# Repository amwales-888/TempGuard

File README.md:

# TempGuard
PID Temperature Controller dsPIC33EV64GM004 Hardware/Firmware 

Initial requirements were to control the temperature of an enclosed system, holding it as close as possible to a set temperature during operation. Venting air out of the enclosure using a FAN would quickly bring the temperature inside the enclosure to match the outside temperature which was unacceptable. Using an MCU we can monitor the temperature and vent air using a fan at a controlled rate. PID algorythms are commonly used in such systems - ['A proportional–integral–derivative controller (PID controller or three-term controller) is a control loop mechanism employing feedback that is widely used in industrial control systems and a variety of other applications requiring continuously modulated control.'](https://en.wikipedia.org/wiki/Proportional%E2%80%93integral%E2%80%93derivative_controller)

[dsPIC33EV64GM004](https://www.microchip.com/en-us/product/dsPIC33EV64GM004) MCU using 20MHz oscllator, configured with 140MHz FOSC ( 70 MIPS ). This device was selected based on pincount, cost and flexibility of its peripherals. It is presented in a surface mount 44pin quad flat pack that is easily hand solderable, along with a respectable 64k of flash and 8k RAM.

- 4 Input Capture devices for interfacing with temp sensors supporting [DHT11](docs/DHT11-Technical-Data-Sheet-Translated-Version-1143054.pdf) and [DHT22](docs/DHT22.pdf) protocols
- 3 2-Channel PWM devices running at 25KHz for controlling [4pin PWN fans](docs/4_Wire_PWM_Spec.pdf). Support for 3pin and 2pin fans using PWM on power pin if required
- 1 UART for communication, loggin with a host, configured at 9600 8N1
- 11 GPIOs connected to [2004 LCD (HD44780)](docs/HD44780.pdf) driven using 8bit Data, RS, RW and Enable, reading busy-flag to ensure maximum output throughput
- 12 GPIOs
  - 2 dedicated to rotary encoder ( GPIO4, GPIO5 )
  - 1 dedicated to a button ( GPIO3 )
  - 3 Inputs used to read TACH from 4PIN and 3PIN fans to calculate RPM 
  - 3 Output to FETs used as low-side switches controlling the FAN 12V power in the case of 3pin and 2pin fans and for power off control of 4pin fans
- 3 spare GPIO0, GPIO1, GPIO2 which can be used for notification of ALARM conditions, ie. FAN not spinning or Sensor not returning data.
- 3 Timers
  - TMR1 used as system timer used to monitor 10ms tick for scheduling
  - TMR3 used by PWM hardware
  - TMR4 used as high frequency timer with 7.3us tick

The system runs with a simple co-operative multitasking round-robin scheduler with a 10ms tick rate and ability to use a second high resultion timer with a 7us period. Tasks can be scheduled with or without a period, added and removed during operation. All tasks are non-blocking.

User interaction is through an LCD display current value from the attached temp sensors and fans. A rotary encoder and button can be used to navigate menus and change settings.

The LCD is updated from an in memory buffer at >120 times a second.

Ouput is also sent via UART over USB for logging purposes.

The firmware was developed usng the Microchip tools, [MPLABX](https://www.microchip.com/en-us/tools-resources/develop/mplab-x-ide) (v6.10) using [XC16](https://www.microchip.com/en-us/tools-resources/develop/mplab-xc-compilers/xc16) (v2.10) compiler and [MCC](https://www.microchip.com/en-us/tools-resources/configure/mplab-code-configurator) (v5) used to generate system, clock and initialisation code for hardware peripherals.

The firmware is written to the MCU in-circuit using a Microchip [Pickit5](https://www.microchip.com/en-us/development-tool/PG164150). Using the Pickit5 it is also possible to do source level debugging of the MCU while in-circuit.

For test and verification the first version of the device was coded on a dsPIC33EV64GM002 28pin DIP version of the device and soldered onto stripboard, the results for a 40minute session were logged, once the enclosure reached the required set temperature their was little to no deviation seen over the 40minutes.

## Hardware/Enclosure

<table>
  <tr>
    <td colspan="2"> </td>
  </tr>
  <tr>
    <td> </td>
    <td> </td>
  </tr>
  <tr>
    <td> </td>
    <td> </td>
  </tr>
  <tr>
    <td> </td>
    <td> </td>
  </tr>
</table>

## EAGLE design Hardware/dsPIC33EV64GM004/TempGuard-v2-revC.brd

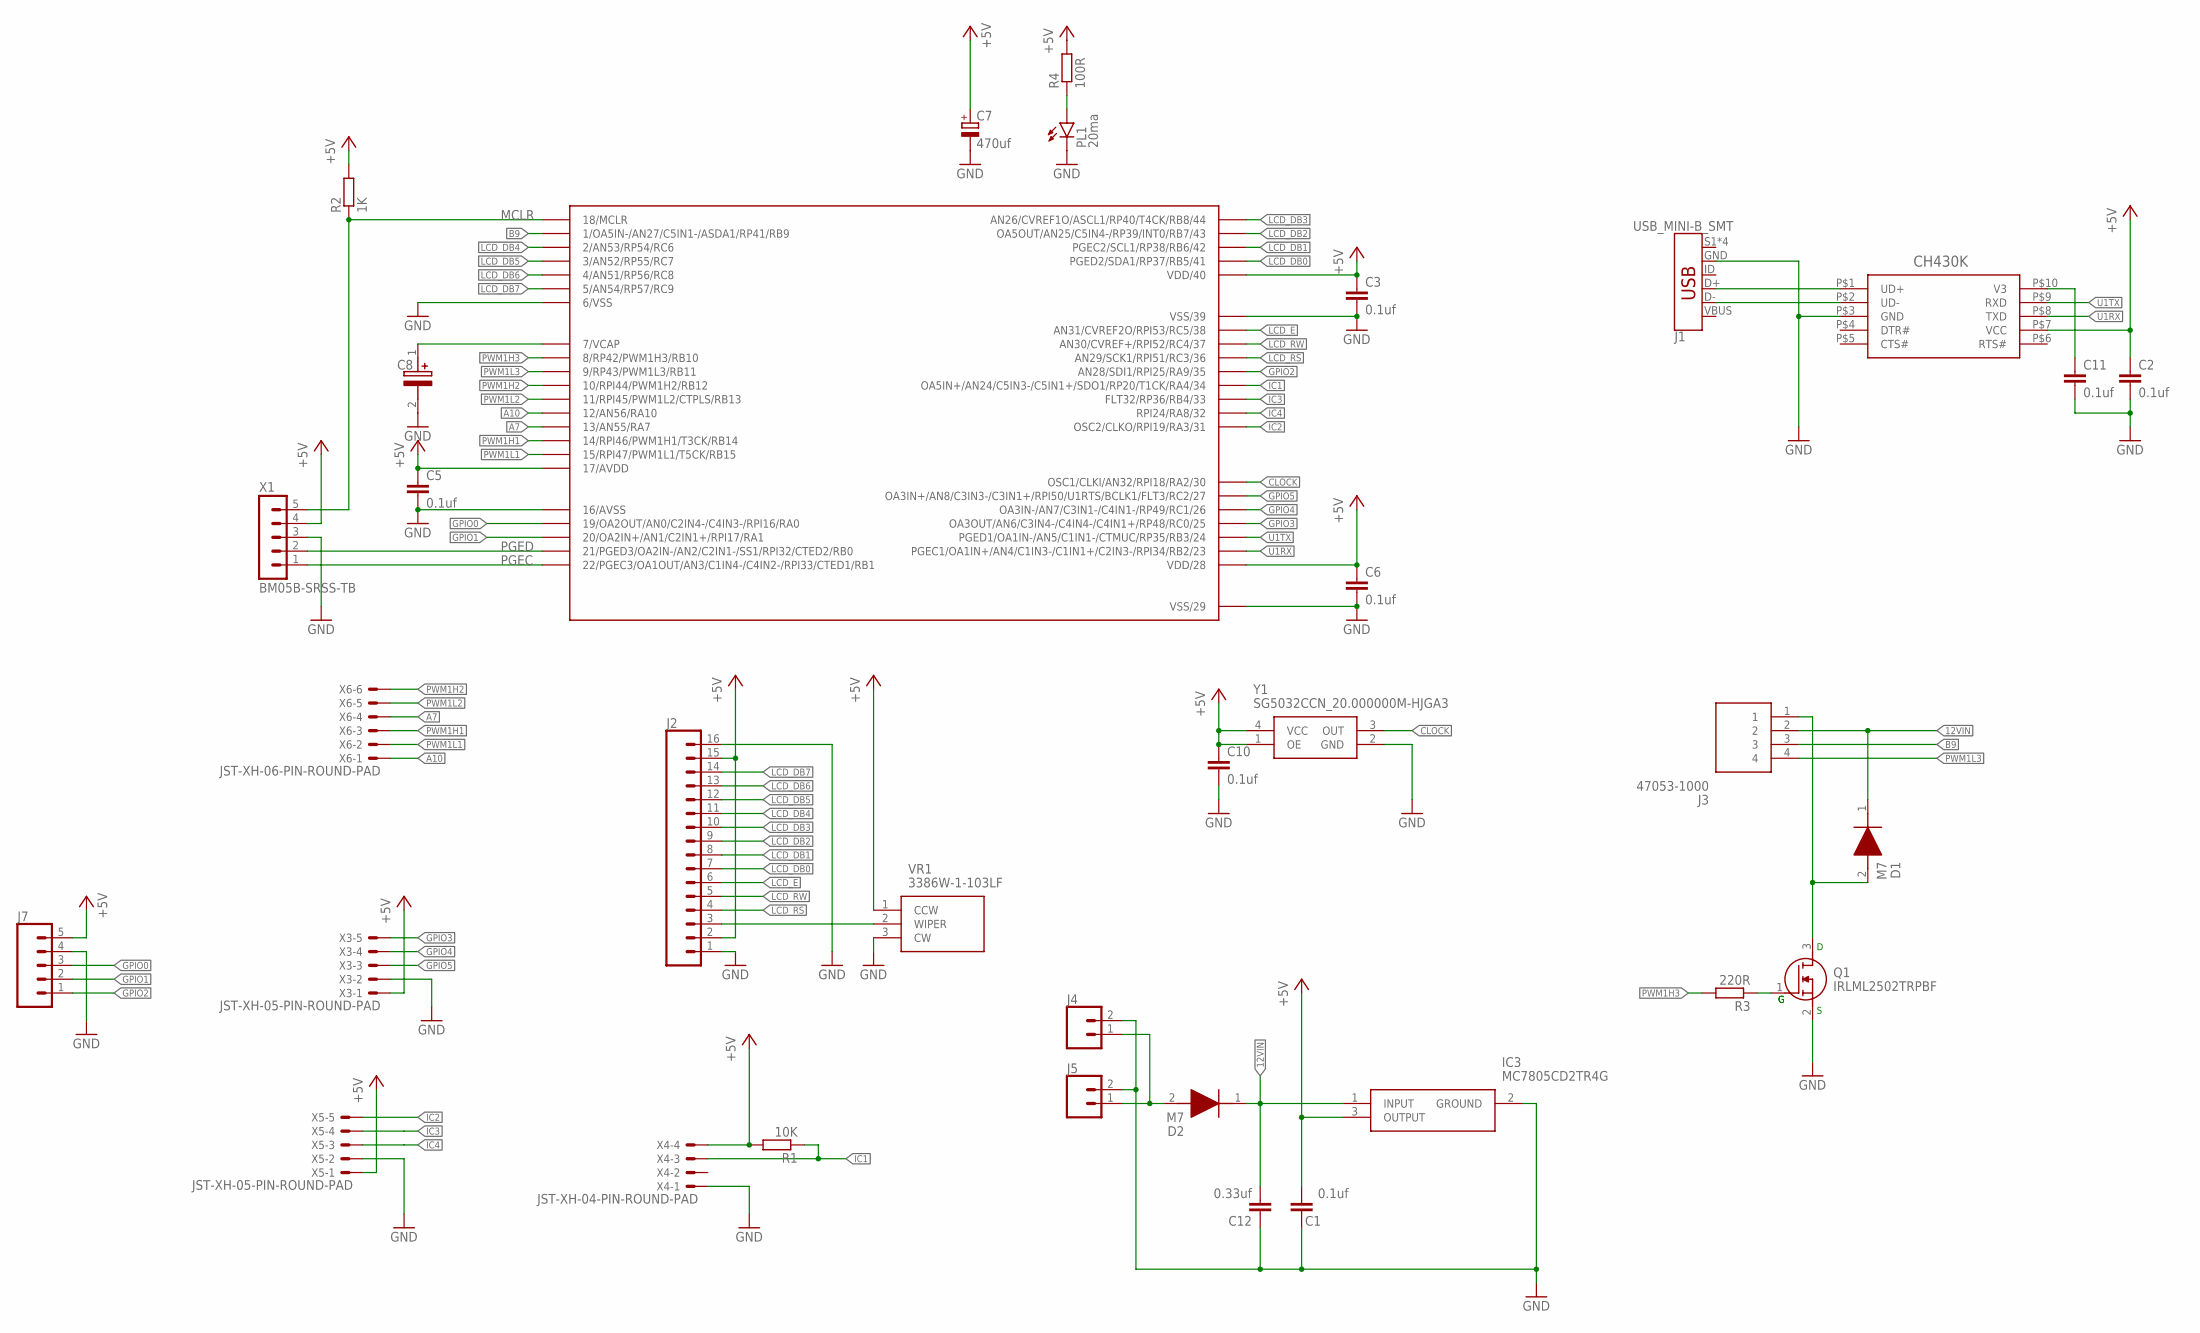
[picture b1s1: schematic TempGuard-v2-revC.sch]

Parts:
C1, C2, C3, C5, C6, C10, C11: 0.1uf; C0805
C7: 470uf; E3,5-8
C8: T491C106K016ATAUTO; T491C
C12: 0.33uf; C1206
D1, D2: M7; DIOM5327X240N
IC3: MC7805CD2TR4G
J1: USB_MINI-B_SMT; USB-MINIB
J2: CONN_16LONGPADS; 1X16_LONGPADS
J3: 47053-1000; 470531000
J4, J5: CONN_025MM; SCREWTERMINAL-5MM-2
J7: CONN_05; 1X05
MCU1: DSPIC33EV64GM004-I/PT; QFP80P1200X1200X120-44
PL1: 20ma; SML0805
Q1: IRLML2502TRPBF; SOT95P237X112-3N
R1: 10K; R0805
R2: 1K; R0805
R3: 220R; R0805
R4: 100R; R0805
U$1: CH430K; ESSOP-10
VR1: 3386W-1-103LF; 3386W
X1: BM05B-SRSS-TB
X3, X5: JST-XH-05-PIN-ROUND-PAD; JST-XH-05-PACKAGE-ROUND-PAD
X4: JST-XH-04-PIN-ROUND-PAD; JST-XH-04-PACKAGE-ROUND-PAD
X6: JST-XH-06-PIN-ROUND-PAD; JST-XH-06-PACKAGE-ROUND-PAD
Y1: SG5032CCN_20.000000M-HJGA3; SG5032CCN20000000MHJGA3

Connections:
12VIN: C12.2, D1.1 (K), D2.1 (K), IC3.1 (INPUT), J3.2
+5V: C1.2, C2.1, C3.1, C5.1, C6.1, C7.+, C10.1, IC3.3 (OUTPUT), J2.2, J2.15, J7.5, MCU1.17 (17/AVDD), MCU1.28 (VDD/28), MCU1.40 (VDD/40), R1.2, R2.2, R4.2, U$1.P$7 (VCC), VR1.1 (CCW), X1.4, X3.1, X4.4, X5.1, Y1.1 (OE), Y1.4 (VCC)
A7: MCU1.13 (13/AN55/RA7), X6.4
A10: MCU1.12 (12/AN56/RA10), X6.1
B9: J3.3, MCU1.1 (1/OA5IN-/AN27/C5IN1-/ASDA1/RP41/RB9)
CLOCK: MCU1.30 (OSC1/CLKI/AN32/RPI18/RA2/30), Y1.3 (OUT)
GND: C1.1, C2.2, C3.2, C5.2, C6.2, C7.-, C8.2 (-), C10.2, C11.2, C12.1, IC3.2 (GROUND), J1.GND, J2.1, J2.16, J4.2, J5.2, J7.4, MCU1.6 (6/VSS), MCU1.16 (16/AVSS), MCU1.29 (VSS/29), MCU1.39 (VSS/39), PL1.C, Q1.2 (S), U$1.P$3 (GND), VR1.3 (CW), X1.3, X3.2, X4.1, X5.2, Y1.2 (GND)
GPIO0: J7.3, MCU1.19 (19/OA2OUT/AN0/C2IN4-/C4IN3-/RPI16/RA0)
GPIO1: J7.2, MCU1.20 (20/OA2IN+/AN1/C2IN1+/RPI17/RA1)
GPIO2: J7.1, MCU1.35 (AN28/SDI1/RPI25/RA9/35)
GPIO3: MCU1.25 (OA3OUT/AN6/C3IN4-/C4IN4-/C4IN1+/RP48/RC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), X3.5
GPIO4: MCU1.26 (OA3IN-/AN7/C3IN1-/C4IN1-/RP49/RC1/26), X3.4
GPIO5: MCU1.27 (OA3IN+/AN8/C3IN3-/C3IN1+/RPI50/U1RTS/BC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), X3.3
IC1: MCU1.34 (OA5IN+/AN24/C5IN3-/C5IN1+/SDO1/RP20/T1C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), R1.1, X4.3
IC2: MCU1.31 (OSC2/CLKO/RPI19/RA3/31), X5.5
IC3: MCU1.33 (FLT32/RP36/RB4/33), X5.4
IC4: MCU1.32 (RPI24/RA8/32), X5.3
LCD_DB0: J2.7, MCU1.41 (PGED2/SDA1/RP37/RB5/41)
LCD_DB1: J2.8, MCU1.42 (PGEC2/SCL1/RP38/RB6/42)
LCD_DB2: J2.9, MCU1.43 (OA5OUT/AN25/C5IN4-/RP39/INT0/RB7/43)
LCD_DB3: J2.10, MCU1.44 (AN26/CVREF1O/ASCL1/RP40/T4CK/RB8/44)
LCD_DB4: J2.11, MCU1.2 (2/AN53/RP54/RC6)
LCD_DB5: J2.12, MCU1.3 (3/AN52/RP55/RC7)
LCD_DB6: J2.13, MCU1.4 (4/AN51/RP56/RC8)
LCD_DB7: J2.14, MCU1.5 (5/AN54/RP57/RC9)
LCD_E: J2.6, MCU1.38 (AN31/CVREF2O/RPI53/RC5/38)
LCD_RS: J2.4, MCU1.36 (AN29/SCK1/RPI51/RC3/36)
LCD_RW: J2.5, MCU1.37 (AN30/CVREF+/RPI52/RC4/37)
MCLR: MCU1.18 (18/MCLR), R2.1, X1.5
unnamed: D1.2 (A), J3.1, Q1.3 (D)
unnamed: J2.3, VR1.2 (WIPER)
unnamed: PL1.A, R4.1
unnamed: Q1.1 (G), R3.1
unnamed: D2.2 (A), J4.1, J5.1
unnamed: C11.1, U$1.P$10 (V3)
PGEC: MCU1.22 (22/PGEC3/OA1OUT/AN3/C1IN4-/C4IN2-/RPI33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), X1.1
PGED: MCU1.21 (21/PGED3/OA2IN-/AN2/C2IN1-/SS1/RPI32/CT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), X1.2
PWM1H1: MCU1.14 (14/RPI46/PWM1H1/T3CK/RB14), X6.3
PWM1H2: MCU1.10 (10/RPI44/PWM1H2/RB12), X6.6
PWM1H3: MCU1.8 (8/RP42/PWM1H3/RB10), R3.2
PWM1L1: MCU1.15 (15/RPI47/PWM1L1/T5CK/RB15), X6.2
PWM1L2: MCU1.11 (11/RPI45/PWM1L2/CTPLS/RB13), X6.5
PWM1L3: J3.4, MCU1.9 (9/RP43/PWM1L3/RB11)
U1RX: MCU1.23 (PGEC1/OA1IN+/AN4/C1IN3-/C1IN1+/C2IN3-/R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), U$1.P$8 (TXD)
U1TX: MCU1.24 (PGED1/OA1IN-/AN5/C1IN1-/CTMUC/RP35/RB3/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), U$1.P$9 (RXD)
USB_N: J1.D-, U$1.P$2 (UD-)
USB_P: J1.D+, U$1.P$1 (UD+)
VBUS: J1.VBUS
VCAP: C8.1 (+), MCU1.7 (7/VCAP)

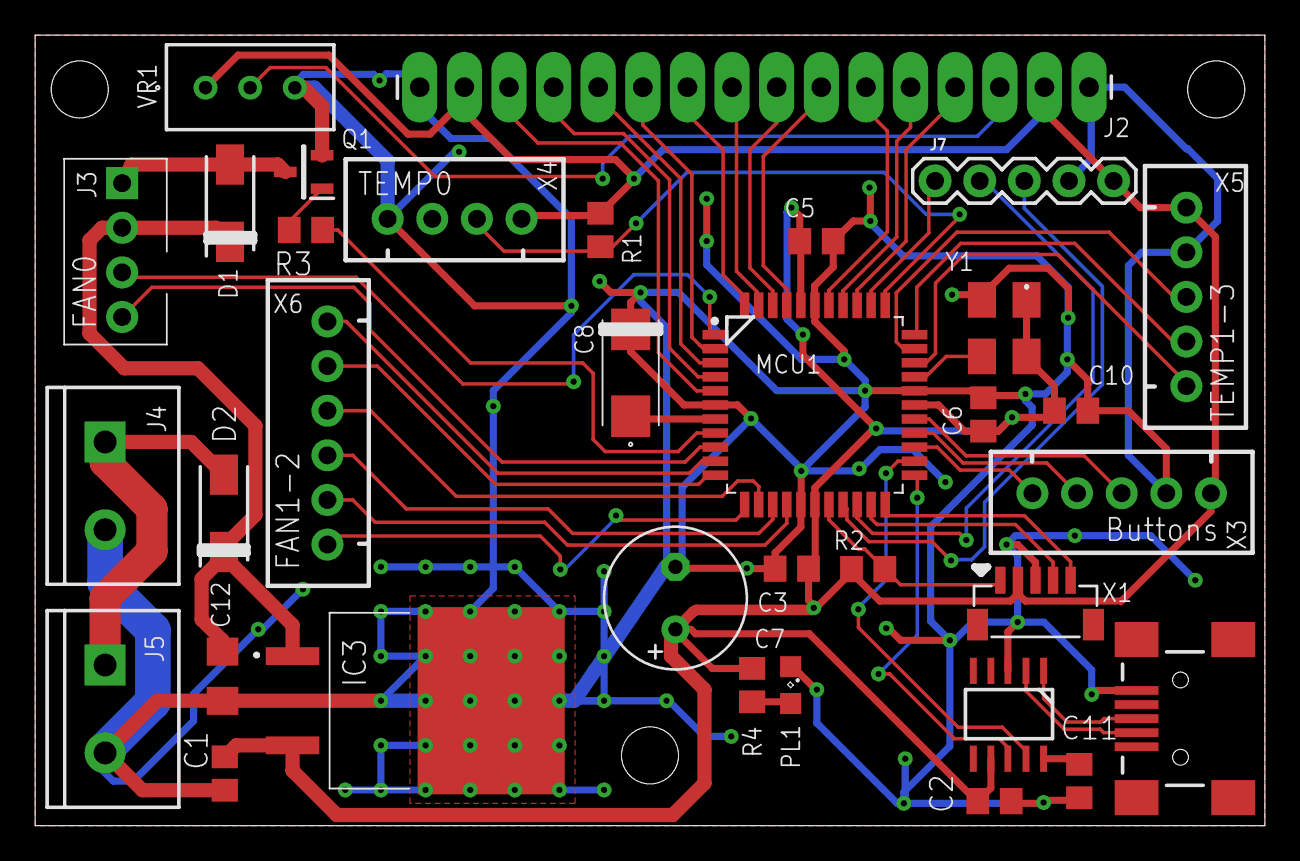
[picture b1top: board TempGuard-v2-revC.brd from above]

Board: 2 copper layers, 70.0 x 45.0 mm, 34 parts (0 on the bottom side), 48 nets.

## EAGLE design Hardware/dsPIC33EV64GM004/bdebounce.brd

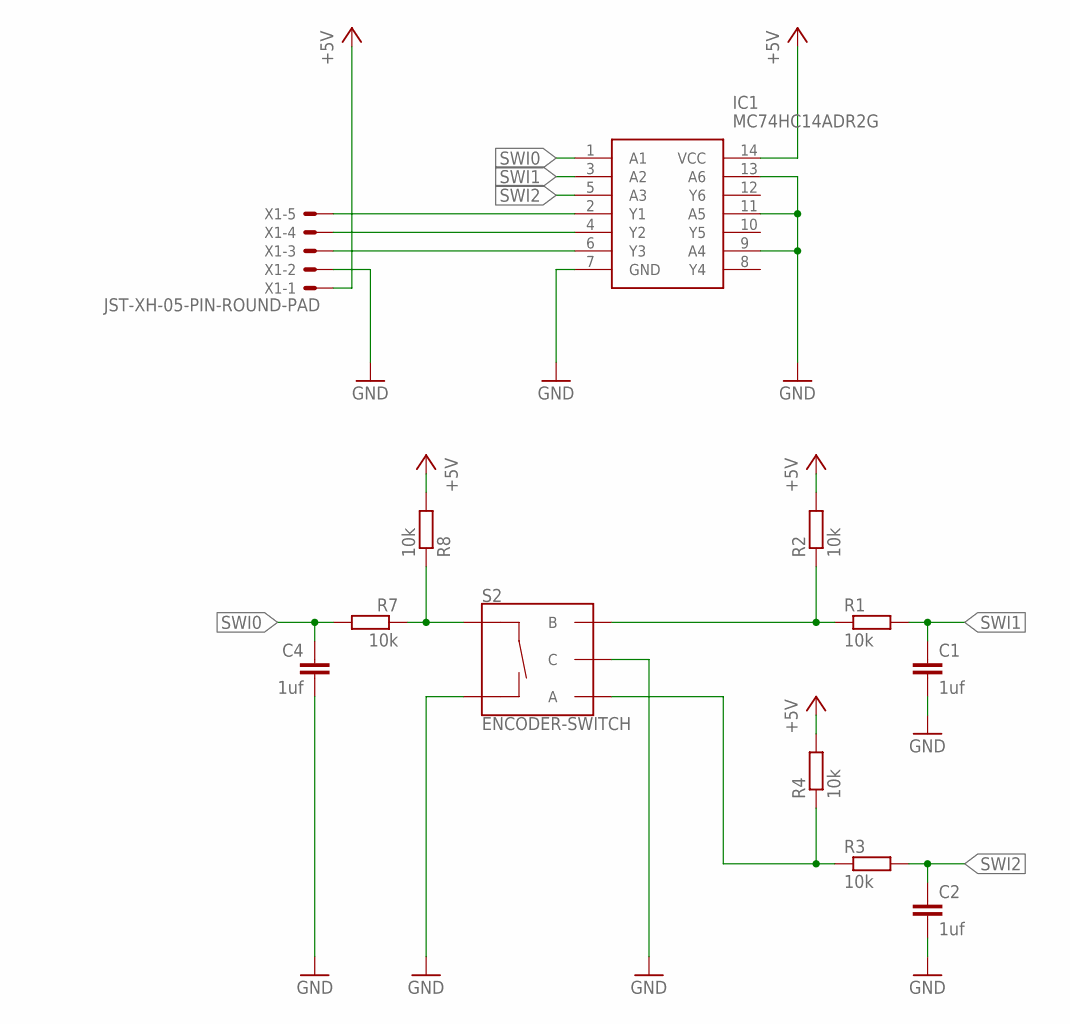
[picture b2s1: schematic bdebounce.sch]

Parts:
C1, C2, C4: 1uf; C0805
IC1: MC74HC14ADR2G; SOIC127P600X175-14N
R1, R2, R3, R4, R7, R8: 10k; R0805
S2: ENCODER-SWITCH; ROTARY_ENC_PLAIN
X1: JST-XH-05-PIN-ROUND-PAD; JST-XH-05-PACKAGE-ROUND-PAD

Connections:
+5V: IC1.14 (VCC), R2.2, R4.2, R8.2, X1.1
GND: C1.2, C2.2, C4.2, IC1.7 (GND), IC1.9 (A4), IC1.11 (A5), IC1.13 (A6), S2.C, S2.SW-, X1.2
unnamed: IC1.6 (Y3), X1.3
SW0: R7.1, R8.1, S2.SW+
SW1: R1.1, R2.1, S2.B
SW2: R3.1, R4.1, S2.A
SWI0: C4.1, IC1.1 (A1), R7.2
SWI1: C1.1, IC1.3 (A2), R1.2
SWI2: C2.1, IC1.5 (A3), R3.2
SWO0: IC1.2 (Y1), X1.5
SWO1: IC1.4 (Y2), X1.4

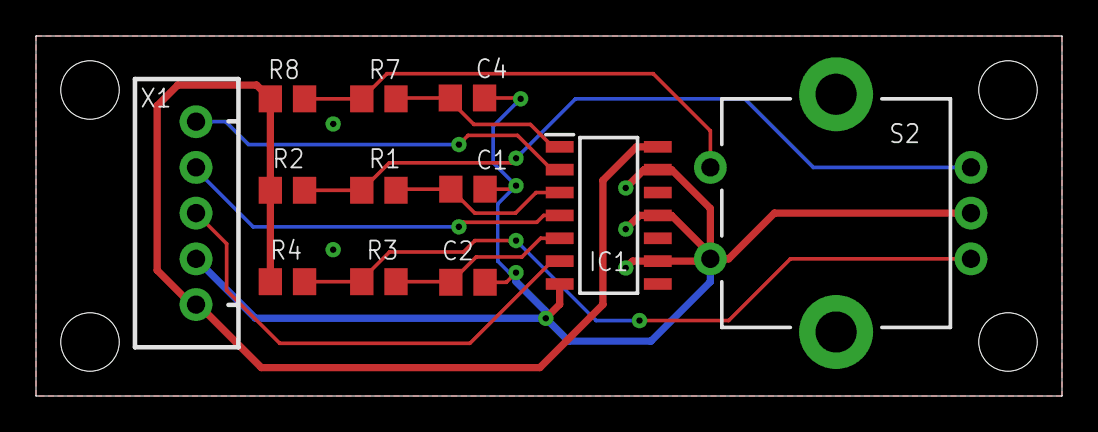
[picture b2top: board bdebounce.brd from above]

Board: 2 copper layers, 57.0 x 20.0 mm, 12 parts (0 on the bottom side), 11 nets.

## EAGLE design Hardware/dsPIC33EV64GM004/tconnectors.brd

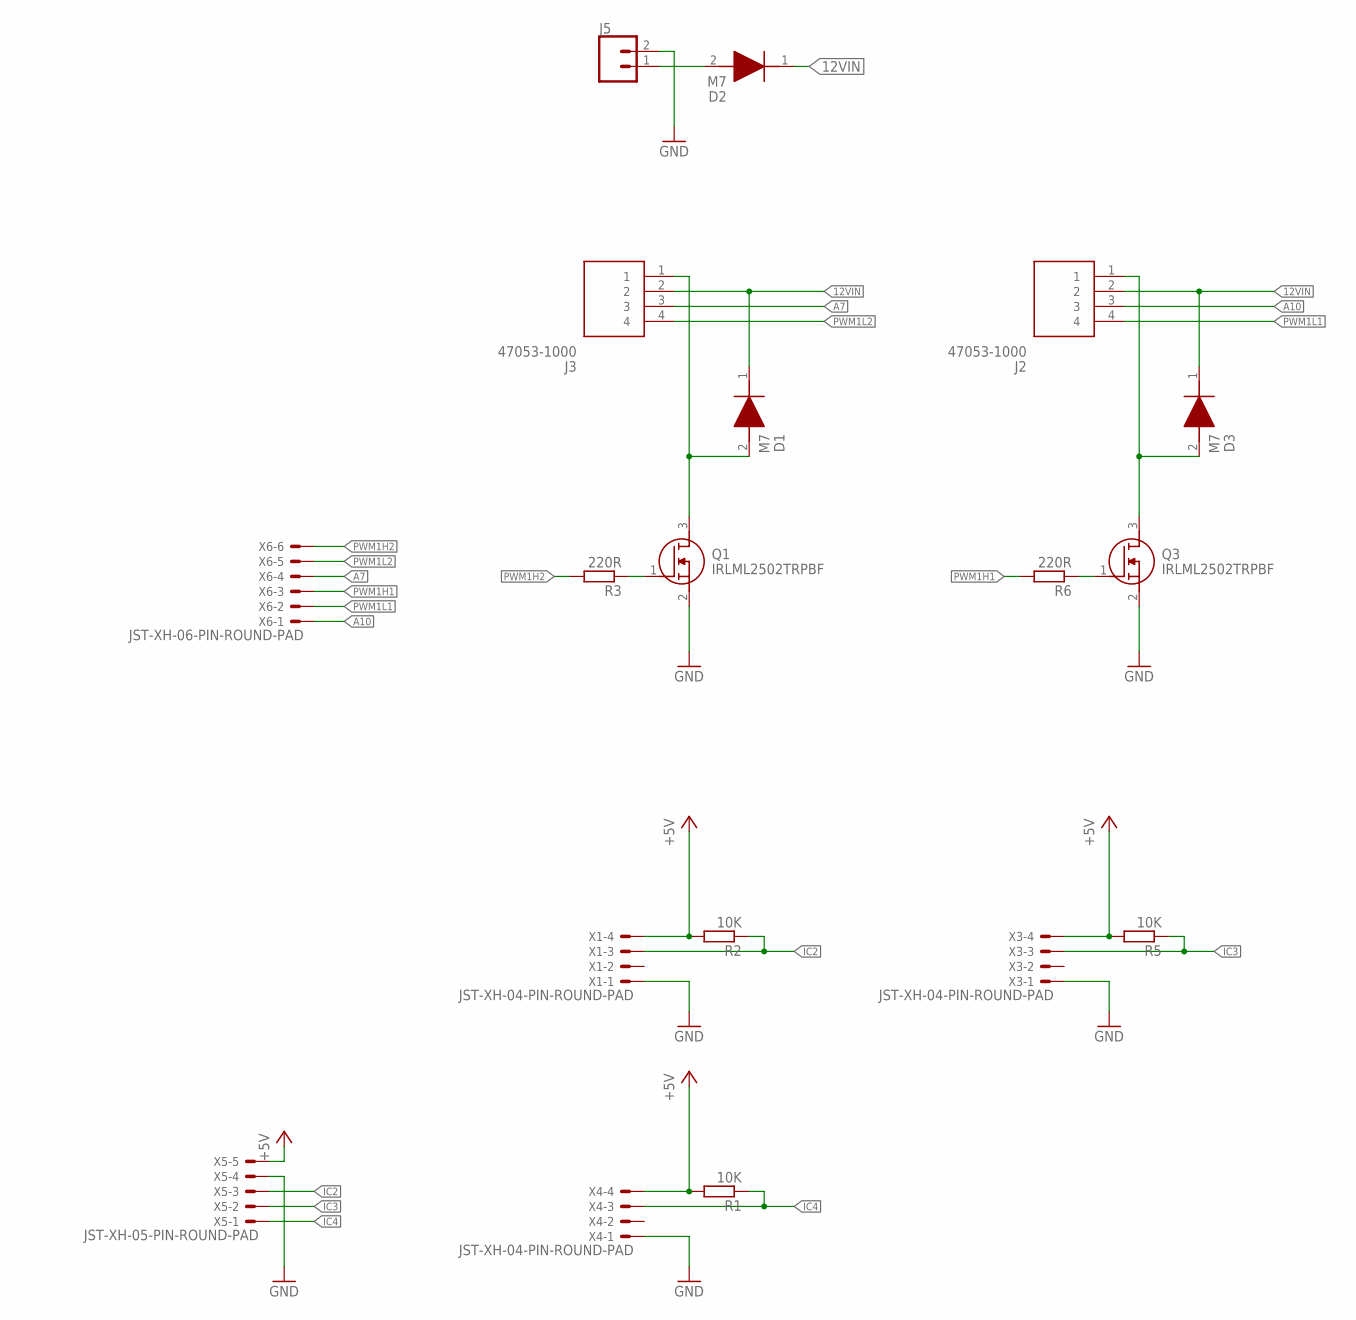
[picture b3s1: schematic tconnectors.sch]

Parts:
D1, D2, D3: M7; DIOM5327X240N
J2, J3: 47053-1000; 470531000
J5: CONN_025MM; SCREWTERMINAL-5MM-2
Q1, Q3: IRLML2502TRPBF; SOT95P237X112-3N
R1, R2, R5: 10K; R0805
R3, R6: 220R; R0805
X1, X3, X4: JST-XH-04-PIN-ROUND-PAD; JST-XH-04-PACKAGE-ROUND-PAD
X5: JST-XH-05-PIN-ROUND-PAD; JST-XH-05-PACKAGE-ROUND-PAD
X6: JST-XH-06-PIN-ROUND-PAD; JST-XH-06-PACKAGE-ROUND-PAD

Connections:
12VIN: D1.1 (K), D2.1 (K), D3.1 (K), J2.2, J3.2
+5V: R1.2, R2.2, R5.2, X1.4, X3.4, X4.4, X5.5
A7: J3.3, X6.4
A10: J2.3, X6.1
GND: J5.2, Q1.2 (S), Q3.2 (S), X1.1, X3.1, X4.1, X5.4
IC2: R2.1, X1.3, X5.3
IC3: R5.1, X3.3, X5.2
IC4: R1.1, X4.3, X5.1
unnamed: D1.2 (A), J3.1, Q1.3 (D)
unnamed: D3.2 (A), J2.1, Q3.3 (D)
unnamed: Q3.1 (G), R6.1
unnamed: Q1.1 (G), R3.1
unnamed: D2.2 (A), J5.1
PWM1H1: R6.2, X6.3
PWM1H2: R3.2, X6.6
PWM1L1: J2.4, X6.2
PWM1L2: J3.4, X6.5

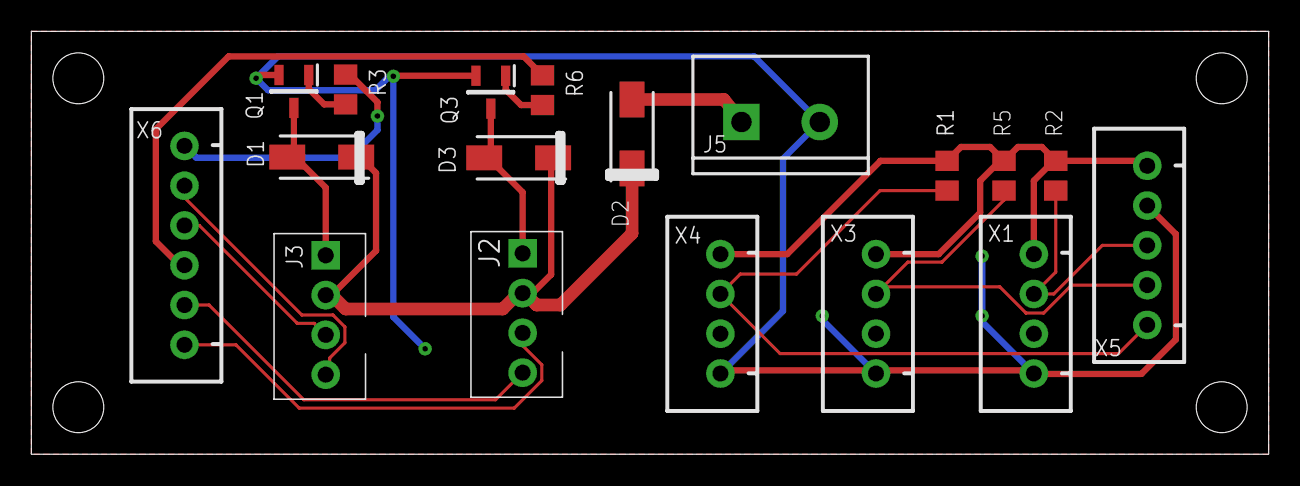
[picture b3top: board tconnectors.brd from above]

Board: 2 copper layers, 79.0 x 27.0 mm, 18 parts (0 on the bottom side), 17 nets.

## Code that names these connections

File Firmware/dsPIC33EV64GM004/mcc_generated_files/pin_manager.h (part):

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*/
/**
  @Summary
    Sets the GPIO pin, RA0, high using LATA0.

  @Description
    Sets the GPIO pin, RA0, high using LATA0.

  @Preconditions
    The RA0 must be set to an output.
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#define GPIO0_SetHigh()          (_LATA0 = 1)
/**
  @Summary
    Sets the GPIO pin, RA0, low using LATA0.

  @Description
    Sets the GPIO pin, RA0, low using LATA0.

  @Preconditions
    The RA0 must be set to an output.
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#define GPIO0_SetLow()           (_LATA0 = 0)
/**
  @Summary
    Toggles the GPIO pin, RA0, using LATA0.

  @Description
    Toggles the GPIO pin, RA0, using LATA0.

  @Preconditions
    The RA0 must be set to an output.
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#define GPIO0_Toggle()           (_LATA0 ^= 1)
/**
  @Summary
    Reads the value of the GPIO pin, RA0.

  @Description
    Reads the value of the GPIO pin, RA0.

  @Preconditions
    None.
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    </code>

*/
#define GPIO0_GetValue()         _RA0
/**
  @Summary
    Configures the GPIO pin, RA0, as an input.

  @Description
    Configures the GPIO pin, RA0, as an input.

  @Preconditions
    None.
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#define GPIO0_SetDigitalInput()  (_TRISA0 = 1)
/**
  @Summary
    Configures the GPIO pin, RA0, as an output.

  @Description
    Configures the GPIO pin, RA0, as an output.

  @Preconditions
    None.
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#define GPIO0_SetDigitalOutput() (_TRISA0 = 0)
/**
  @Summary
    Sets the GPIO pin, RA1, high using LATA1.

  @Description
    Sets the GPIO pin, RA1, high using LATA1.

  @Preconditions
    The RA1 must be set to an output.
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#define GPIO1_SetHigh()          (_LATA1 = 1)
/**
  @Summary
    Sets the GPIO pin, RA1, low using LATA1.

  @Description
    Sets the GPIO pin, RA1, low using LATA1.

  @Preconditions
    The RA1 must be set to an output.
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#define GPIO1_SetLow()           (_LATA1 = 0)
/**
  @Summary
    Toggles the GPIO pin, RA1, using LATA1.

  @Description
    Toggles the GPIO pin, RA1, using LATA1.

  @Preconditions
    The RA1 must be set to an output.
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#define GPIO1_Toggle()           (_LATA1 ^= 1)
/**
  @Summary
    Reads the value of the GPIO pin, RA1.

  @Description
    Reads the value of the GPIO pin, RA1.

  @Preconditions
    None.
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    </code>

*/
#define GPIO1_GetValue()         _RA1
/**
  @Summary
    Configures the GPIO pin, RA1, as an input.

  @Description
    Configures the GPIO pin, RA1, as an input.

  @Preconditions
    None.
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#define GPIO1_SetDigitalInput()  (_TRISA1 = 1)
/**
  @Summary
    Configures the GPIO pin, RA1, as an output.

  @Description
    Configures the GPIO pin, RA1, as an output.

  @Preconditions
    None.
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#define GPIO1_SetDigitalOutput() (_TRISA1 = 0)
/**
  @Summary
    Sets the GPIO pin, RA10, high using LATA10.

  @Description
    Sets the GPIO pin, RA10, high using LATA10.

  @Preconditions
    The RA10 must be set to an output.
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#define TACH2_SetHigh()          (_LATA10 = 1)
/**
  @Summary
    Sets the GPIO pin, RA10, low using LATA10.

  @Description
    Sets the GPIO pin, RA10, low using LATA10.

  @Preconditions
    The RA10 must be set to an output.
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#define TACH2_SetLow()           (_LATA10 = 0)
/**
  @Summary
    Toggles the GPIO pin, RA10, using LATA10.

  @Description
    Toggles the GPIO pin, RA10, using LATA10.

  @Preconditions
    The RA10 must be set to an output.
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#define TACH2_Toggle()           (_LATA10 ^= 1)
/**
  @Summary
    Reads the value of the GPIO pin, RA10.

  @Description
    Reads the value of the GPIO pin, RA10.

  @Preconditions
    None.
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    </code>

*/
#define TACH2_GetValue()         _RA10
/**
  @Summary
    Configures the GPIO pin, RA10, as an input.

  @Description
    Configures the GPIO pin, RA10, as an input.

  @Preconditions
    None.
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#define TACH2_SetDigitalInput()  (_TRISA10 = 1)
/**
  @Summary
    Configures the GPIO pin, RA10, as an output.

  @Description
    Configures the GPIO pin, RA10, as an output.

  @Preconditions
    None.
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#define TACH2_SetDigitalOutput() (_TRISA10 = 0)
/**
  @Summary
    Sets the GPIO pin, RA7, high using LATA7.

  @Description
    Sets the GPIO pin, RA7, high using LATA7.

  @Preconditions
    The RA7 must be set to an output.
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#define TACH1_SetHigh()          (_LATA7 = 1)
/**
  @Summary
    Sets the GPIO pin, RA7, low using LATA7.

  @Description
    Sets the GPIO pin, RA7, low using LATA7.

  @Preconditions
    The RA7 must be set to an output.
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#define TACH1_SetLow()           (_LATA7 = 0)
/**
  @Summary
    Toggles the GPIO pin, RA7, using LATA7.

  @Description
    Toggles the GPIO pin, RA7, using LATA7.

  @Preconditions
    The RA7 must be set to an output.
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#define TACH1_Toggle()           (_LATA7 ^= 1)
/**
  @Summary
    Reads the value of the GPIO pin, RA7.

  @Description
    Reads the value of the GPIO pin, RA7.

  @Preconditions
    None.
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    </code>

*/
#define TACH1_GetValue()         _RA7
/**
  @Summary
    Configures the GPIO pin, RA7, as an input.

  @Description
    Configures the GPIO pin, RA7, as an input.

  @Preconditions
    None.
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#define TACH1_SetDigitalInput()  (_TRISA7 = 1)
/**
  @Summary
    Configures the GPIO pin, RA7, as an output.

  @Description
    Configures the GPIO pin, RA7, as an output.

  @Preconditions
    None.
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#define TACH1_SetDigitalOutput() (_TRISA7 = 0)
/**
  @Summary
    Sets the GPIO pin, RA9, high using LATA9.

  @Description
    Sets the GPIO pin, RA9, high using LATA9.

  @Preconditions
    The RA9 must be set to an output.
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#define GPIO2_SetHigh()          (_LATA9 = 1)
/**
  @Summary
    Sets the GPIO pin, RA9, low using LATA9.

  @Description
    Sets the GPIO pin, RA9, low using LATA9.

  @Preconditions
    The RA9 must be set to an output.
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#define GPIO2_SetLow()           (_LATA9 = 0)
/**
  @Summary
    Toggles the GPIO pin, RA9, using LATA9.

  @Description
    Toggles the GPIO pin, RA9, using LATA9.

  @Preconditions
    The RA9 must be set to an output.
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#define GPIO2_Toggle()           (_LATA9 ^= 1)
/**
  @Summary
    Reads the value of the GPIO pin, RA9.

  @Description
    Reads the value of the GPIO pin, RA9.

  @Preconditions
    None.
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    </code>

*/
#define GPIO2_GetValue()         _RA9
/**
  @Summary
    Configures the GPIO pin, RA9, as an input.

  @Description
    Configures the GPIO pin, RA9, as an input.

  @Preconditions
    None.
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#define GPIO2_SetDigitalInput()  (_TRISA9 = 1)
/**
  @Summary
    Configures the GPIO pin, RA9, as an output.

  @Description
    Configures the GPIO pin, RA9, as an output.

  @Preconditions
    None.
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#define GPIO2_SetDigitalOutput() (_TRISA9 = 0)
/**
  @Summary
    Sets the GPIO pin, RB5, high using LATB5.

  @Description
    Sets the GPIO pin, RB5, high using LATB5.

  @Preconditions
    The RB5 must be set to an output.
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#define LCD_DB0_SetHigh()          (_LATB5 = 1)
/**
  @Summary
    Sets the GPIO pin, RB5, low using LATB5.

  @Description
    Sets the GPIO pin, RB5, low using LATB5.

  @Preconditions
    The RB5 must be set to an output.
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#define LCD_DB0_SetLow()           (_LATB5 = 0)
/**
  @Summary
    Toggles the GPIO pin, RB5, using LATB5.

  @Description
    Toggles the GPIO pin, RB5, using LATB5.

  @Preconditions
    The RB5 must be set to an output.
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#define LCD_DB0_Toggle()           (_LATB5 ^= 1)
/**
  @Summary
    Reads the value of the GPIO pin, RB5.

  @Description
    Reads the value of the GPIO pin, RB5.

  @Preconditions
    None.
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    </code>

*/
#define LCD_DB0_GetValue()         _RB5
/**
  @Summary
    Configures the GPIO pin, RB5, as an input.

  @Description
    Configures the GPIO pin, RB5, as an input.

  @Preconditions
    None.
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#define LCD_DB0_SetDigitalInput()  (_TRISB5 = 1)
/**
  @Summary
    Configures the GPIO pin, RB5, as an output.

  @Description
    Configures the GPIO pin, RB5, as an output.

  @Preconditions
    None.
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#define LCD_DB0_SetDigitalOutput() (_TRISB5 = 0)
/**
  @Summary
    Sets the GPIO pin, RB6, high using LATB6.

  @Description
    Sets the GPIO pin, RB6, high using LATB6.

  @Preconditions
    The RB6 must be set to an output.
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#define LCD_DB1_SetHigh()          (_LATB6 = 1)
/**
  @Summary
    Sets the GPIO pin, RB6, low using LATB6.

  @Description
    Sets the GPIO pin, RB6, low using LATB6.

  @Preconditions
    The RB6 must be set to an output.
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#define LCD_DB1_SetLow()           (_LATB6 = 0)
/**
  @Summary
    Toggles the GPIO pin, RB6, using LATB6.

  @Description
    Toggles the GPIO pin, RB6, using LATB6.

  @Preconditions
    The RB6 must be set to an output.
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#define LCD_DB1_Toggle()           (_LATB6 ^= 1)
/**
  @Summary
    Reads the value of the GPIO pin, RB6.

  @Description
    Reads the value of the GPIO pin, RB6.

  @Preconditions
    None.
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    </code>

*/
#define LCD_DB1_GetValue()         _RB6
/**
  @Summary
    Configures the GPIO pin, RB6, as an input.

  @Description
    Configures the GPIO pin, RB6, as an input.

  @Preconditions
    None.
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#define LCD_DB1_SetDigitalInput()  (_TRISB6 = 1)
/**
  @Summary
    Configures the GPIO pin, RB6, as an output.

  @Description
    Configures the GPIO pin, RB6, as an output.

  @Preconditions
    None.
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#define LCD_DB1_SetDigitalOutput() (_TRISB6 = 0)
/**
  @Summary
    Sets the GPIO pin, RB7, high using LATB7.

  @Description
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
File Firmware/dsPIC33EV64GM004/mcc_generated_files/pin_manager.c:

/**
  PIN MANAGER Generated Driver File

  @Company:
    Microchip Technology Inc.

  @File Name:
    pin_manager.c

  @Summary:
    This is the generated manager file for the PIC24 / dsPIC33 / PIC32MM MCUs device.  This manager
    configures the pins direction, initial state, analog setting.
    The peripheral pin select, PPS, configuration is also handled by this manager.

  @Description:
    This source file provides implementations for PIN MANAGER.
    Generation Information :
        Product Revision  :  PIC24 / dsPIC33 / PIC32MM MCUs - 1.171.4
        Device            :  dsPIC33EV64GM004
    The generated drivers are tested against the following:
        Compiler          :  XC16 v2.10
        MPLAB 	          :  MPLAB X v6.05
*/

/*
    (c) 2020 Microchip Technology Inc. and its subsidiaries. You may use this
    software and any derivatives exclusively with Microchip products.

    THIS SOFTWARE IS SUPPLIED BY MICROCHIP "AS IS". NO WARRANTIES, WHETHER
    EXPRESS, IMPLIED OR STATUTORY, APPLY TO THIS SOFTWARE, INCLUDING ANY IMPLIED
    WARRANTIES OF NON-INFRINGEMENT, MERCHANTABILITY, AND FITNESS FOR A
    PARTICULAR PURPOSE, OR ITS INTERACTION WITH MICROCHIP PRODUCTS, COMBINATION
    WITH ANY OTHER PRODUCTS, OR USE IN ANY APPLICATION.

    IN NO EVENT WILL MICROCHIP BE LIABLE FOR ANY INDIRECT, SPECIAL, PUNITIVE,
    INCIDENTAL OR CONSEQUENTIAL LOSS, DAMAGE, COST OR EXPENSE OF ANY KIND
    WHATSOEVER RELATED TO THE SOFTWARE, HOWEVER CAUSED, EVEN IF MICROCHIP HAS
    BEEN ADVISED OF THE POSSIBILITY OR THE DAMAGES ARE FORESEEABLE. TO THE
    FULLEST EXTENT ALLOWED BY LAW, MICROCHIP'S TOTAL LIABILITY ON ALL CLAIMS IN
    ANY WAY RELATED TO THIS SOFTWARE WILL NOT EXCEED THE AMOUNT OF FEES, IF ANY,
    THAT YOU HAVE PAID DIRECTLY TO MICROCHIP FOR THIS SOFTWARE.

    MICROCHIP PROVIDES THIS SOFTWARE CONDITIONALLY UPON YOUR ACCEPTANCE OF THESE
    TERMS.
*/


/**
    Section: Includes
*/

#include <xc.h>
#include <stdio.h>
#include "pin_manager.h"

/**
 Section: File specific functions
*/
void (*CN_InterruptHandler)(void) = NULL;

/**
 Section: Driver Interface Function Definitions
*/
void PIN_MANAGER_Initialize (void)
{
    /****************************************************************************
     * Setting the Output Latch SFR(s)
     ***************************************************************************/
    LATA = 0x0000;
    LATB = 0x0008;
    LATC = 0x0000;

    /****************************************************************************
     * Setting the GPIO Direction SFR(s)
     ***************************************************************************/
    TRISA = 0x059C;
    TRISB = 0x0217;
    TRISC = 0x0007;

    /****************************************************************************
     * Setting the Weak Pull Up and Weak Pull Down SFR(s)
     ***************************************************************************/
    CNPDA = 0x0000;
    CNPDB = 0x0000;
    CNPDC = 0x0000;
    CNPUA = 0x0480;
    CNPUB = 0x0200;
    CNPUC = 0x0000;

    /****************************************************************************
     * Setting the Open Drain SFR(s)
     ***************************************************************************/
    ODCA = 0x0000;
    ODCB = 0x0000;
    ODCC = 0x0000;

    /****************************************************************************
     * Setting the Analog/Digital Configuration SFR(s)
     ***************************************************************************/
    ANSELA = 0x0000;
    ANSELB = 0x0000;
    ANSELC = 0x0000;
    
    /****************************************************************************
     * Set the PPS
     ***************************************************************************/
    __builtin_write_OSCCONL(OSCCON & 0xbf); // unlock PPS

    RPINR7bits.IC1R = 0x0014;    //RA4->IC1:IC1
    RPINR8bits.IC4R = 0x0018;    //RA8->IC4:IC4
    RPOR0bits.RP35R = 0x0001;    //RB3->UART1:U1TX
    RPINR8bits.IC3R = 0x0024;    //RB4->IC3:IC3
    RPINR7bits.IC2R = 0x0013;    //RA3->IC2:IC2
    RPINR18bits.U1RXR = 0x0022;    //RB2->UART1:U1RX

    __builtin_write_OSCCONL(OSCCON | 0x40); // lock PPS
    
    /****************************************************************************
     * Interrupt On Change: any
     ***************************************************************************/
    CNENAbits.CNIEA10 = 1;    //Pin : RA10
    CNENAbits.CNIEA7 = 1;    //Pin : RA7
    CNENBbits.CNIEB9 = 1;    //Pin : RB9
    
    /* Initialize IOC Interrupt Handler*/
    CN_SetInterruptHandler(&CN_CallBack);
    
    /****************************************************************************
     * Interrupt On Change: Interrupt Enable
     ***************************************************************************/
    IFS1bits.CNIF = 0; //Clear CNI interrupt flag
    IEC1bits.CNIE = 1; //Enable CNI interrupt
}

void __attribute__ ((weak)) CN_CallBack(void)
{

}

void CN_SetInterruptHandler(void (* InterruptHandler)(void))
{ 
    IEC1bits.CNIE = 0; //Disable CNI interrupt
    CN_InterruptHandler = InterruptHandler; 
    IEC1bits.CNIE = 1; //Enable CNI interrupt
}

void CN_SetIOCInterruptHandler(void *handler)
{ 
    CN_SetInterruptHandler(handler);
}

/* Interrupt service routine for the CNI interrupt. */
void __attribute__ (( interrupt, no_auto_psv )) _CNInterrupt ( void )
{
    if(IFS1bits.CNIF == 1)
    {
        if(CN_InterruptHandler) 
        { 
            CN_InterruptHandler(); 
        }
        
        // Clear the flag
        IFS1bits.CNIF = 0;
    }
}

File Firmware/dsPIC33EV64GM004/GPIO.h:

/* 
 *  Copyright (c) 2023 Angelo Masci
 * 
 * Permission is hereby granted, free of charge, to any person obtaining a copy
 * of this software and associated documentation files (the "Software"), to deal
 * in the Software without restriction, including without limitation the rights
 * to use, copy, modify, merge, publish, distribute, sublicense, and/or sell
 * copies of the Software, and to permit persons to whom the Software is
 * furnished to do so, subject to the following conditions:
 * 
 * The above copyright notice and this permission notice shall be included in all
 * copies or substantial portions of the Software.
 * 
 * THE SOFTWARE IS PROVIDED "AS IS", WITHOUT WARRANTY OF ANY KIND, EXPRESS OR
 * IMPLIED, INCLUDING BUT NOT LIMITED TO THE WARRANTIES OF MERCHANTABILITY,
 * FITNESS FOR A PARTICULAR PURPOSE AND NONINFRINGEMENT. IN NO EVENT SHALL THE
 * AUTHORS OR COPYRIGHT HOLDERS BE LIABLE FOR ANY CLAIM, DAMAGES OR OTHER
 * LIABILITY, WHETHER IN AN ACTION OF CONTRACT, TORT OR OTHERWISE, ARISING FROM,
 * OUT OF OR IN CONNECTION WITH THE SOFTWARE OR THE USE OR OTHER DEALINGS IN THE
 * SOFTWARE.
 * 
 */

#ifndef GPIO_H
#define	GPIO_H

//#include <xc.h> // include processor files - each processor file is guarded.  
#include <stdint.h>

#define MAXGPIOS 6

/* GPIO Id Map
 * 
 * GPIO0 -> A0
 * GPIO1 -> A1
 * GPIO2 -> A9
 * GPIO3 -> C0
 * GPIO4 -> C1
 * GPIO5 -> C2
 * 
 */

enum GPIODirection_e {
    
    GPIOOutput=0,  
    GPIOInput,
};

enum GPIOType {
    
    GPIODigital=0,  
    GPIOAnalog,
};

#ifdef	__cplusplus
extern "C" {
#endif /* __cplusplus */

uint8_t GPIOGetValue(uint16_t id);
void GPIOSetValue(uint16_t id, uint8_t value);
void GPIOSetDirection(uint16_t id, enum GPIODirection_e direction);
void GPIOSetType(uint16_t id, enum GPIOType type);
void GPIOToggleValue(uint16_t id);
void GPIOEnablePullDown(uint16_t id);
void GPIODisablePullDown(uint16_t id);
void GPIOEnablePullUp(uint16_t id);
void GPIODisablePullUp(uint16_t id);

#ifdef	__cplusplus
}
#endif /* __cplusplus */

#endif	/* GPIO_H */

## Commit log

2024-10-29 Initial project checkin
2024-10-30 Update README.md
    reformat and add table

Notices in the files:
parts and their libraries:
SparkFun-Connectors: Licensing: Creative Commons ShareAlike 4.0 International - https://creativecommons.org/licenses/by-sa/4.0
